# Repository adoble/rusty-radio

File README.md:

# Rusty Radio

An embedded internet radio written in Rust.

> **⚠️ Work In Progress**
>
> This project is under active development. Features, hardware, and software may change frequently. 

## Supported Formats

Rusty Radio currently supports:
- MP3
- AAC
- M3U

## System Diagram

## Hardware
 - For the radio uses the Seeed Studio [XIAO ESP32C-C3](https://wiki.seeedstudio.com/XIAO_ESP32C3_Getting_Started/) for its external antenna, making the radio independent of the enclosure.
 - For the user interface (display, tuning knob and preset buttons) uses another XIAO ESP32-C3 which communicates over an UART interface with the radio processor. 
   This approach was chosen as using C3 (or for that matter, a S3) for both the radio and the display led to memory issues.  
- Uses the VS1053 chip to decode the streamed audio.
- Schematics are created using KiCad 9.0.

## Software Architecture

- Built with `esp-hal` and [Embassy](https://dev.to/theembeddedrustacean/embassy-on-esp-getting-started-27fi) for async task scheduling.
- Project scaffolded using `cargo generate esp-rs/esp-template`. See the [GitHub repo](https://github.com/esp-rs/esp-template). The software project root is `controller`.

## Development Notes

- Embassy code examples are referenced from [esp-hal examples](https://github.com/esp-rs/esp-hal/tree/main/examples/src/bin).
- For more on Embassy, see the [Embassy Book](https://embassy.dev/book/).

---

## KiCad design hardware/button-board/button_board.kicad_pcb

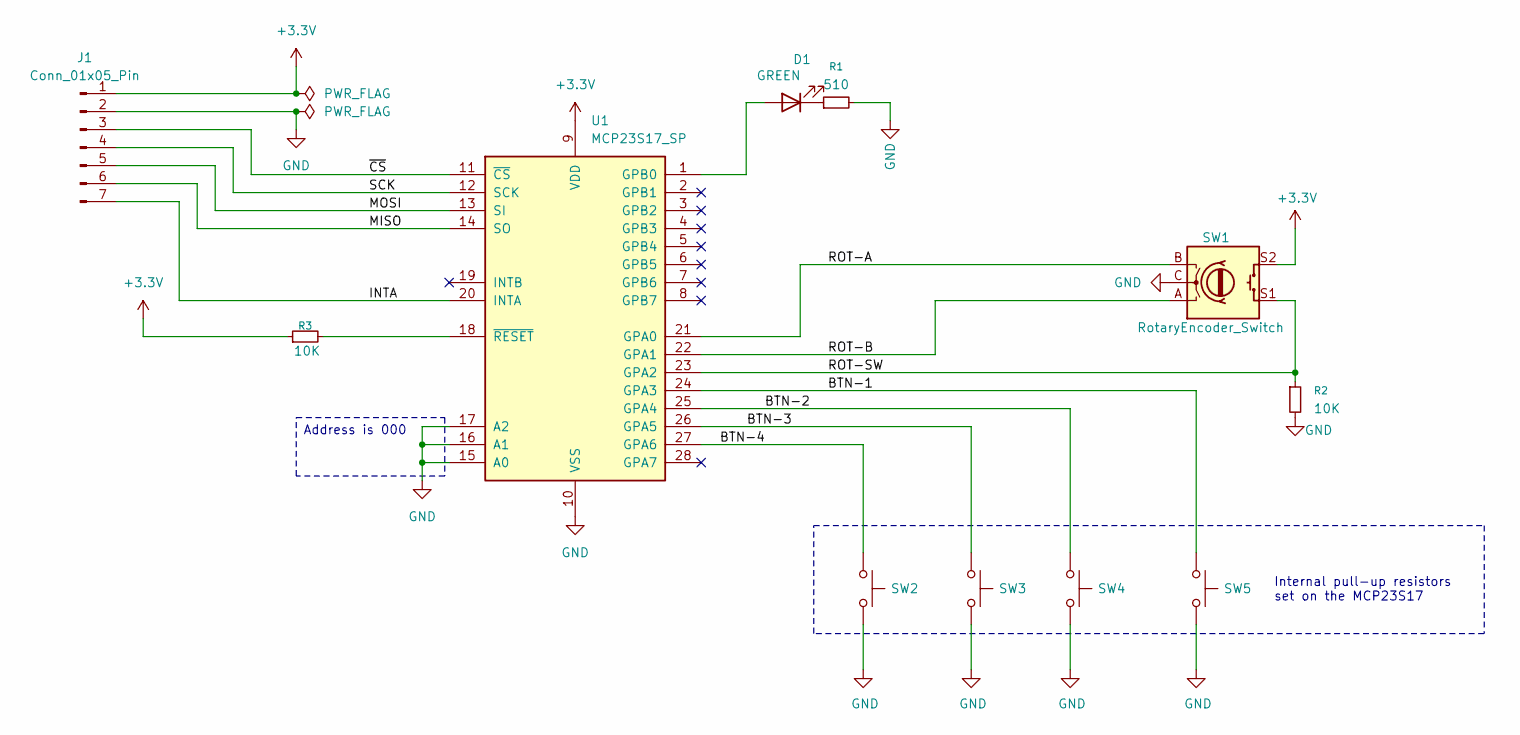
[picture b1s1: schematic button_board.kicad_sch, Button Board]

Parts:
D1: GREEN; D_T-1_P2.54mm_Vertical_AnodeUp
J1: Conn_01x05_Pin; PinHeader_1x07_P2.54mm_Vertical
R1: 510; R_Axial_DIN0207_L6.3mm_D2.5mm_P5.08mm_Vertical
R2, R3: 10K; R_Axial_DIN0207_L6.3mm_D2.5mm_P5.08mm_Vertical
SW1: RotaryEncoder_Switch; RotaryEncoder_Alps_EC11E-Switch_Vertical_H20mm
SW2, SW3, SW4, SW5: SW_Push; SW_Tactile_Straight_KSA0Axx1LFTR
U1: MCP23S17_SP; DIP-28_W7.62mm

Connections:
+3.3V: J1.1, R3.1, SW1.S2, U1.9 (VDD)
/BTN-1: SW5.1, U1.24 (GPA3)
/BTN-2: SW4.1, U1.25 (GPA4)
/BTN-3: SW3.1, U1.26 (GPA5)
/BTN-4: SW2.1, U1.27 (GPA6)
/INTA: J1.7, U1.20 (INTA)
/MISO: J1.6, U1.14 (SO)
/MOSI: J1.5, U1.13 (SI)
/ROT-A: SW1.B, U1.21 (GPA0)
/ROT-B: SW1.A, U1.22 (GPA1)
/ROT-SW: R2.1, SW1.S1, U1.23 (GPA2)
/SCK: J1.4, U1.12 (SCK)
/~CS: J1.3, U1.11 (~CS)
GND: J1.2, R1.2, R2.2, SW1.C, SW2.2, SW3.2, SW4.2, SW5.2, U1.10 (VSS), U1.15 (A0), U1.16 (A1), U1.17 (A2)
unnamed: D1.2 (A), U1.1 (GPB0)
unnamed: D1.1 (K), R1.1
unnamed: R3.2, U1.18 (~RESET)

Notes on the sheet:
Internal pull-up resistors set on the MCP23S17
Address is 000

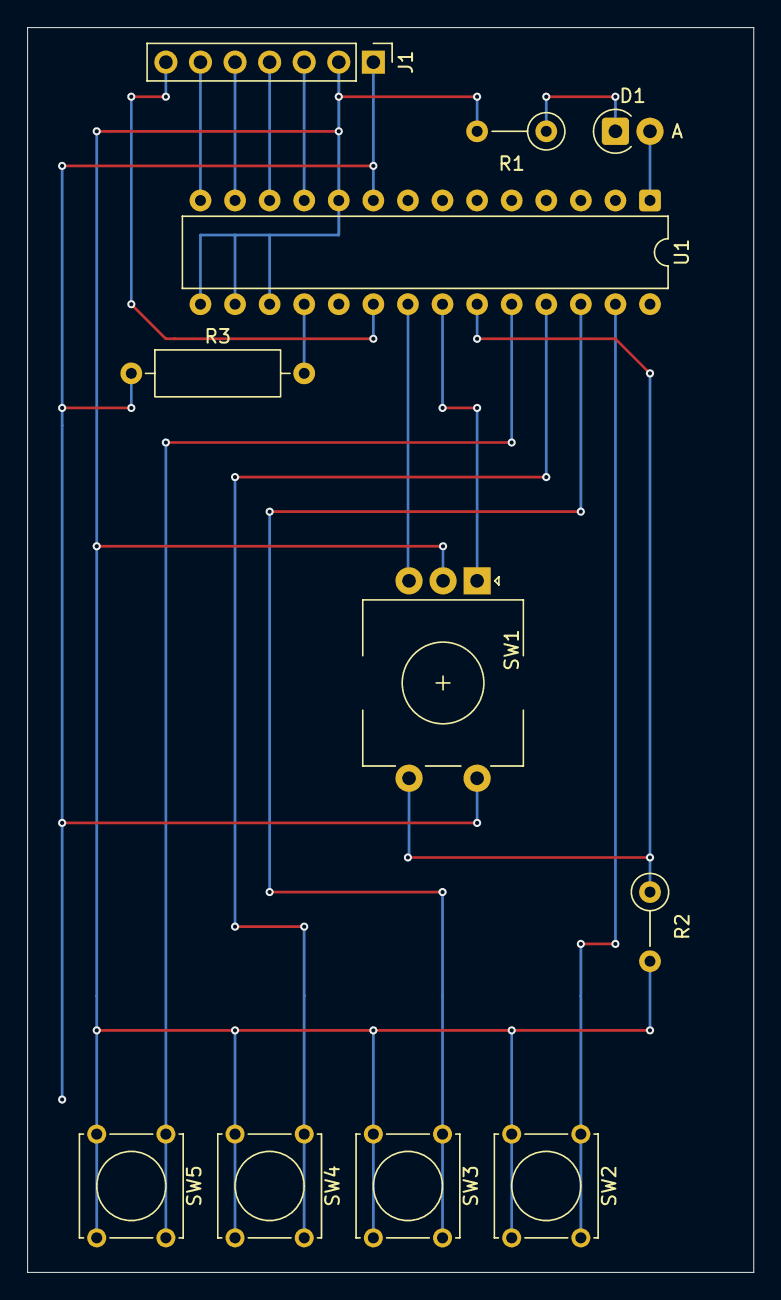
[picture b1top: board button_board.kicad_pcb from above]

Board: 2 copper layers, 53.3 x 91.4 mm, 11 parts (0 on the bottom side), 17 nets.

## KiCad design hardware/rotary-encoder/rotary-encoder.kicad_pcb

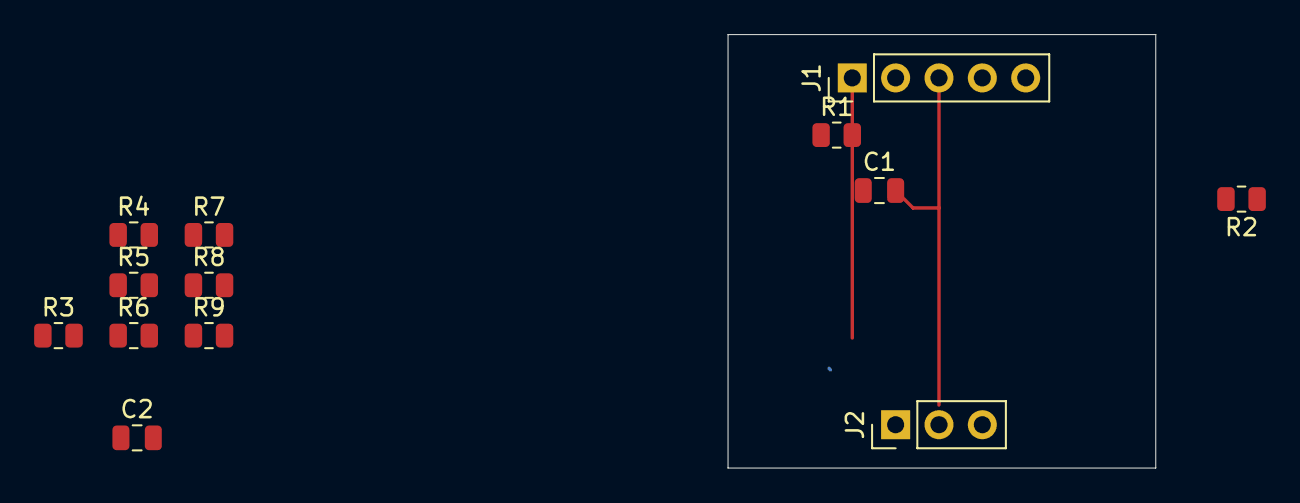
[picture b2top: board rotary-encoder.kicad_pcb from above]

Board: 2 copper layers, 25.1 x 25.4 mm, 13 parts (0 on the bottom side), 9 nets.

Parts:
C1, C2: 10n; C_0805_2012Metric
J1: Conn_01x05; PinHeader_1x05_P2.54mm_Vertical
J2: Conn_01x03; PinHeader_1x03_P2.54mm_Vertical
R1, R2: 1k; R_0805_2012Metric
R3, R4, R5, R6, R7, R8, R9: 100K; R_0805_2012Metric

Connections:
+3.3V: J2.1, R1.1, R2.1
GND: C1.2, C2.2, J1.3, J2.3, R7.1
unnamed: C1.1, J1.1, R1.2, R3.1
unnamed: C2.1, J1.5, R2.2, R4.1
unnamed: R3.2, R5.1
unnamed: R4.2, R6.1
unnamed: R5.2, R8.2, R9.1
unnamed: R7.2, R8.1
OUT: J2.2, R6.2, R9.2

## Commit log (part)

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2024-11-11 Initial from template
2024-11-11 Embassy - first working code
2024-11-12 Regenerated for C3
2024-11-12 Embassy dependencies
2024-11-12 Embassy hello world example
2024-11-12 Toggle pin in task
2024-11-13 Candidate HTTP client crates
2024-11-13 Button input
2024-11-13 RGB LED
2024-11-13 HTTP no-std example
2024-11-14 Updated for wifi example
2024-11-14 Added dependencies - code builds
2024-11-14 Establishes connection to WiFi
2024-11-15 Updated with video ref
2024-11-15 Refactored bing task to async task
2024-11-15 Refactor: Changed variable names
2024-11-15 Refactor: Moved wifi scan as not required
2024-11-15 Wifi connect as async function
2024-11-15 Use new_with_mode
2024-11-16 Updated to embassy-net api
2024-11-16 Wifi connection done asynchronously
2024-11-16 Network stack running
2024-11-16 Updated with example code link
2024-11-16 Todo
2024-11-16 Debounced button
2024-11-16 Added embassy-sync
2024-11-16 Added signalling
2024-11-16 Solved problem with different embedded-nal-async
2024-11-18 Increaed task arean size
2024-11-18 Increased number of sockets
2024-11-20 Can read web page!
2024-11-20 Updated comment to give advice about number of sockets
2024-11-20 Static assertions
2024-11-20 Proper random number generation
2024-11-20 Streamed reading over http
2024-11-23 Schematic used for development
2024-11-23 Removed some unused dependencies
2024-11-23 Added channel
2024-11-25 Set uu SPI and mutex
2024-11-25 Mover te mp3 resources
2024-11-25 Skeleton VS1053 driver
2024-11-27 Project restructured
2024-11-27 Deleted redundant test directory
2024-11-28 sci_read passes first test
2024-11-28 sci_read returns u16
2024-11-28 sci_write
2024-11-28 Added Registers enum
2024-11-29 Removed mp3cs
2024-11-29 Added wait for dreq
2024-11-29 Added reset pin
2024-11-29 Conversions for registers and constants
2024-11-29 Added
2024-11-30 Added reset fucntionality and set_volume
2024-11-30 Register and Mode tests
2024-11-30 set_volume
2024-11-30 dump_registers()
2024-12-04 Added button and led
2024-12-13 Driver basics work and use of shared-bus
2024-12-14 Updated notes in comments
2024-12-14 Updated dependencies and required code, config changes
2024-12-16 Added async_delay to project
2024-12-16 Changed power wiring
2024-12-16 dump_registers seems to work
2024-12-16 Test and correct set_volume
2024-12-17 Vs1053Driver::begin() works
2024-12-17 sine_test implemented. Does not seem to work.
2024-12-18 sample_rate
2024-12-18 Tidied up comments etc.
2024-12-18 added play_data
2024-12-29 DOES NOT COMPILE
2025-01-17 Updated to version esp-hal 0.23.1
2025-01-17 Removed redundant module
2025-01-17 Updated schematic comments
2025-01-18 Added print_registers function
2025-01-19 Refactored main
2025-01-19 Tidied up the imports
2025-01-19 Create LICENSE
2025-01-20 Added pulse_spi for troubleshooting
2025-01-20 Moved main to front + clippy warnings corrected
2025-01-20 Comment outt pulse_spi, spi clock observed
2025-01-20 Spi works
2025-01-24 Test music not static
2025-01-26 Spurious 'MUSIC_CHANNEL not used' warning stopped
2025-01-29 Project name change
2025-01-29 impl Send for sharing
2025-01-29 Kicad spurious changes
2025-01-30 Moved access_radio_stations to task
2025-01-30 Refactored some tasks.
2025-01-30 display_web_content moved to tasks
2025-01-30 Moved out wifi tasks
2025-04-05 Kicad migration to Linux
2025-04-05 Migrated code as initial codebase
2025-04-06 Changed station to one that does not do redirects
2025-04-06 Update .gitignore to ignnore KiCad temporary files
2025-04-06 Can read headers using reqwless
2025-04-15 Added http-builder
2025-04-15 Switched back to more basic http handling
2025-04-15 Changed reading a bit
2025-04-16 Added http-builder for rust-analyzer
2025-04-17 Correctly builds http request
2025-04-17 Increased BUFFER_SIZE. Can now hear chopped up music
2025-04-22 Another failed attempt to use reqwless
2025-04-22 Checking fill status of music channel.
2025-04-22 Changed music channel message length to 32
2025-04-23 Tidy up unused stuff
2025-04-24 Removed system_monitor as not used
2025-04-24 Change to using Pipe instead of Channel
2025-04-24 Removed notification task
2025-04-24 Added initial fill of buffer
2025-04-25 Partially functioning, but slow version with stats
2025-04-26 Commented out initial fill loop and adjusts diagnostic measurements
2025-04-26 Local server & reinstated initial_fill loop
2025-04-26 Merged initial_fill loop into main loop
2025-04-26 Using write_all to pipe
2025-04-28 Powering of the VS1053
2025-05-01 Fetches from git with GitHub Personal Access Token
2025-05-01 Updated to esp-hal version 0.23.1. Compiles
2025-05-04 Schematic for XIAO version
2025-05-10 Updated schematic to get around XIAO pin restrictions
2025-05-12 perf: optimize WiFi and streaming performance
    Hardware:
    - Switch target board from ESP32-C3-DevKit-M to Seeed XIAO ESP32C3
    WiFi Optimizations:
    - Tune WiFi buffer sizes and queue lengths
    - Enable AMPDU for both RX and TX
    - Set RX/TX queue sizes (20/5)
2025-05-12 Tided code and lint
2025-05-12 LED shows when all has been initialised
2025-05-12 Station is parameter osfstream
2025-05-13 Restructure stream
2025-05-13 [feat] Handle redirects from a HTTP response
    Function:
    - Handles redirects when accessing an internet radio station.
    Code Structure:
    - Split streaming logic into separate functions
    - Add proper type safety with heapless::String
    Testing:
2025-05-14 LED indicates when wifi has been connected
2025-05-15 Skeleton for Stations data structure
2025-05-15 Initial integration of Stations into the main corpus of the code.
2025-05-23 Better repsonse status code handling
2025-05-23 Tidied up
2025-05-23 Refactored streaming with better redirect handling
2025-05-23 Prep for multiple stations
2025-05-30 Solved lack of memory problem
2025-05-30 AUDIO_BUFFER_SIZE const refactored
2025-05-30 Simple stations change
2025-05-30 Immediate startup
2025-05-30 Tuner task skeleton
2025-05-31 Initial station over Watch
2025-05-31 Station and Stations use static and compressed data
2025-05-31 Simple station change with new Stations structure
2025-05-31 feat: Can cycle through stations
2025-06-01 Removed redundant code
2025-06-02 Sketch of rotary encoder 'one-pin' board
2025-06-02 Added espflash configuration files
2025-06-02 Added music_type
2025-06-03 M3U reading kind of works, but still errors
2025-06-06 Terminate function
2025-06-07 feat: Read M3U files
2025-06-09 Protoboard layout
2025-06-09 Removing changes for later overwrite
2025-06-09 Button board design
2025-06-10 Bump version
2025-06-10 Prep for error handling
2025-06-10 Prep for error handling
2025-06-10 Removed panics, error messages etc.
2025-06-11 Errors are recoverable
2025-06-14 Dependency mcp23s17-async
2025-06-22 Corrected error with fn button_pressed
2025-06-23 Preset buttons work (without interrupt logic)
2025-06-23 Removed warnings
2025-06-23 Rotary encoder wiring consistent with bitton-board
2025-06-29 New station data structure integrated with rest.
2025-06-30 Can read the rotary encoder
2025-06-30 Added notes for future development
2025-07-02 Station name length was not handiing real world conditions
2025-07-02 Some stations were https which is not supported
2025-07-02 Rotary encoder works, but is unreliable!
2025-07-03 New algorithm
2025-07-03 Added movement to algorithm
2025-07-03 Experiment - added arms
2025-07-05 Simplified error handling
2025-07-06 New tuning scheme implemented
2025-07-06 Error Handled
2025-07-06 Added station indicator LED control
2025-07-06 Renamed tuner2 to tuner
2025-07-06 Tuner as mod
2025-07-06 Extracted tuning scale
2025-07-06 Doc warning
2025-07-06 Better response
2025-07-07 Added delay before asserting RST low.
2025-07-07 Preperation for conditional compilation
2025-07-07 Statistics code is only conditionally compiled
2025-07-07 Corrected range too large error
2025-07-07 Removed debug statements
2025-07-07 Tidy
2025-07-08 Corrected preset positioning problem
2025-07-08 Removed no preset set message
2025-07-08 Removed a preset
2025-07-08 Reinstated preset 3
2025-07-25 Wifi updated
2025-07-25 Upgraded - only the driver locking needs to be modified.
2025-07-29 Reverting back to the locked driver technique
2025-07-29 Bumped version - Using esp-hal version 1.0.0-rc.0
2025-07-29 Sendable abapter for the mcp23s17 driver
2025-08-04 Skeleton read_stations function
2025-08-04 Refactor types and constants
2025-08-04 Error handling skeleton
2025-08-10 Restructured. Code compiles but does not run correctly
2025-08-28 Display added to schematic + RESET_CODEC + R_SW_PU symbol
2025-08-28 Wiring changes to RESET_CODEC
2025-08-30 Rejected using 5V for display + comments
2025-09-25 Added display SPI isolator
2025-10-01 5V power for display
2025-10-01 Display chip select
2025-10-02 Added ra8875 driver
2025-12-02 Aborted UI integration
2025-12-03 Updated to esp-hal 1.0.0
2025-12-03 Corrected the initialization order (particularly for wifi)
2025-12-03 lint
2025-12-05 Added todo note
2025-12-30 UART command design
2025-12-30 Code updates for esp-hal version 1.0.0
2026-01-18 Added xiao esp32-S3 symbol to project library
2026-01-23 Compiles for esp32s3 (xtensa architecture)
2026-01-23 Radio works with esp32s3! But cannot change stations
2026-01-24 Station changes work. Debug code removed.
2026-01-25 Commented out tests that did not compile
2026-01-26 Correctly displays tuned station
2026-01-26 Temporary station indicator activated
2026-01-30 Added UOIcommands to sync.rs
2026-02-20 Set correct target for xtensa-esp32s3-none-elf
2026-03-20 Changed signal names from display to ui
2026-03-20 Updated schematic page settings
2026-03-27 Significantly reduced the size of the body buffer
2026-03-27 Bumped version
2026-03-27 Updated system diagram
2026-04-02 Migration to C3 and front panel removal completed
2026-04-02 Refactored app pcakage to radio package
2026-04-06 Added ui skeleton
2026-04-09 Intergrated front panel
2026-04-09 Removed some redundancies
2026-04-11 Added uart-handler. Removed profile.
2026-04-11 Added uart-handler
2026-04-11 Basic skeleton for uart-handler
2026-04-11 Updated the commands
2026-04-12 Basic set_station function
2026-04-13 Extended set_station to return the station name
2026-04-14 Own error type
2026-04-14 Refactored error handling
2026-04-14 Added Command and conversion
2026-04-15 Refactored Command into seperate file
2026-04-15 Removed function send_hallo as no longer required
2026-04-15 Refactored into the struct UartHandler
2026-04-15 Extracted send_command()
2026-04-17 Completed handling of ACK response and tests
2026-04-17 Updated inter-processor communication protocol
2026-04-17 Refactored to have RadioControlProtocol as top level (lib) module
2026-04-17 Moved command tests to uart_handler tests
2026-04-17 Refactored tests
2026-04-17 Extended RadionControlProtocol tests
2026-04-18 Added set_preset and query_config
2026-04-18 Replaced Command::stringify with From trait and directly converted to bytes
2026-04-20 Initial skeleton for task receive_radio_control_commands
2026-04-20 Added try_from to Command
2026-04-26 Remove all uart logic as the approach was not working
2026-05-28 Update/Correction of comments
2026-05-28 Added RADIO_COMMANDS_CHANNEL
2026-06-02 Updated spec
2026-06-03 Changed module structure to avoid overusing mod.rs
2026-06-03 Set up UART
2026-06-03 Version updates
2026-06-04 Changed workspaces to avoid dependency confilicts
2026-06-04 Added correct version of esp-bootloader-esp-idf
2026-06-05 Initial functioning station selection
2026-06-06 Updated uart_handler with function send_ack and send_error, i.e. receiver side functions
2026-06-07 Added acknowledge_set_station
2026-06-10 Updated with achnowledge_set_station() and documentation
2026-06-10 Added static-assertion to check that MAX_NUMBER_PARMETERS is not zero
2026-06-10 Using log instead of espprintln
2026-06-14 Refactor: Moved StationConfig to crate radio_control_protocol
2026-06-14 Ignore tarpaulin test coverage reports
2026-06-16 Synchronisation between async tasks
2026-06-16 Refactored and removed the mutex on uart
2026-06-18 Loads station config
2026-06-22 Skeleton uart mock
2026-06-22 Draft version of mock_uart
2026-06-25 Partially functioning mock-uart
2026-06-26 Removed mock_uart, restored to working version
